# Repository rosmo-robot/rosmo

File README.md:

# Rosmo
 Rosmo Hardware
 For documentation see [https://rosmo-robot.github.io/](https://rosmo-robot.github.io/)

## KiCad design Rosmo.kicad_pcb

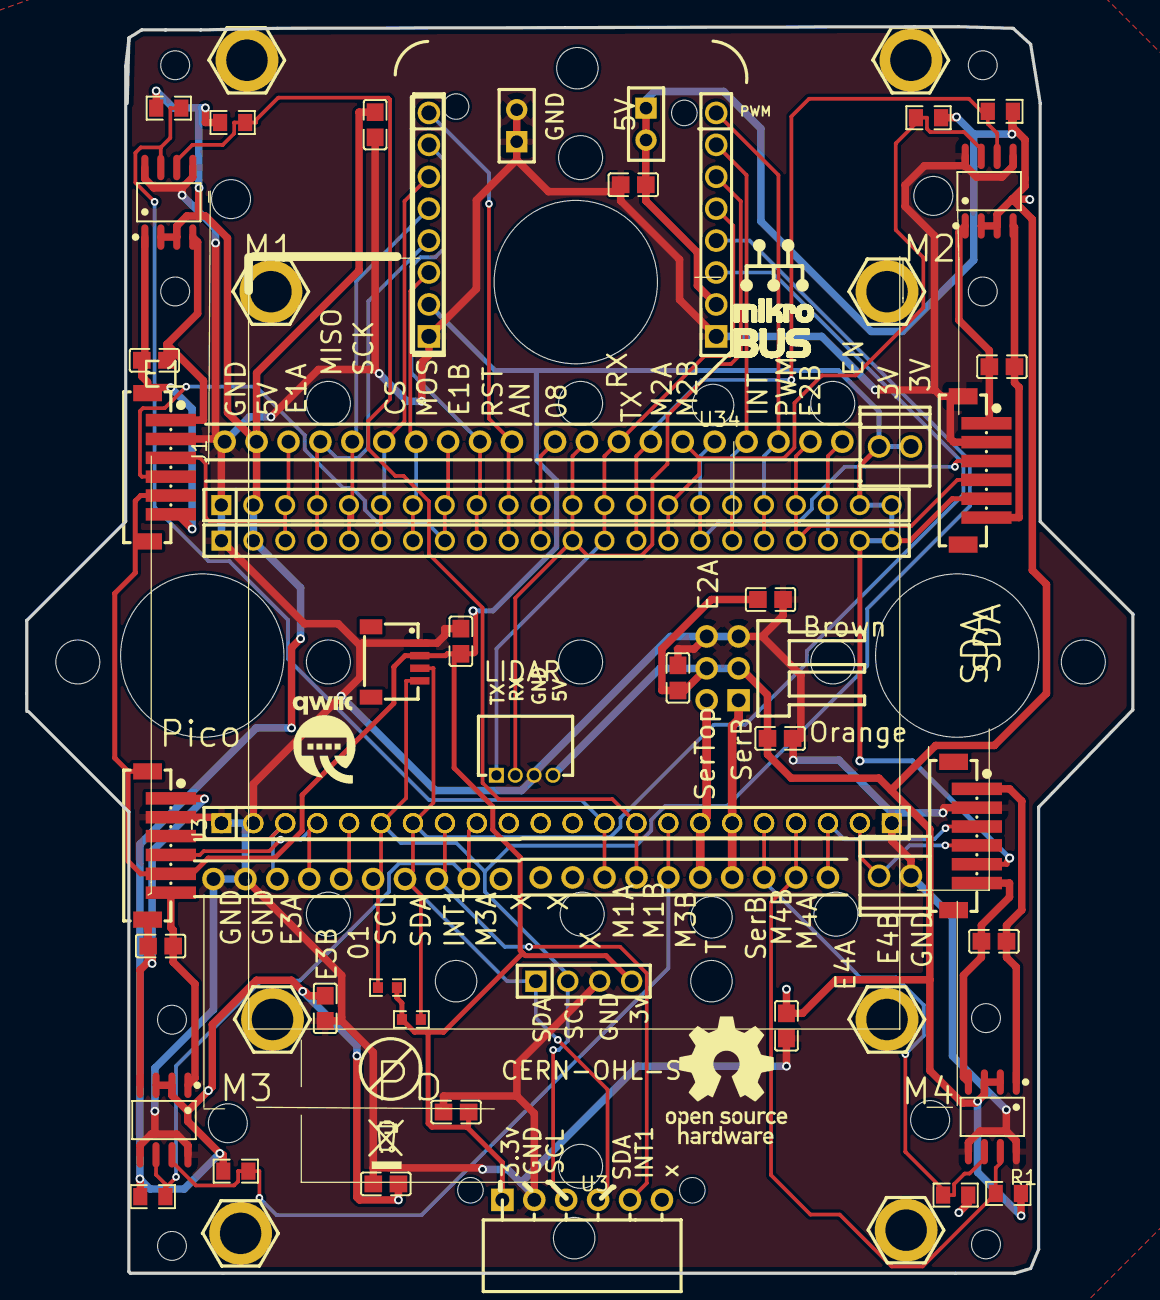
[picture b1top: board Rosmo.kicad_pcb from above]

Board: 2 copper layers, 88.0 x 99.2 mm, 78 parts (0 on the bottom side), 45 nets.

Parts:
.5: OPENSOURCE-LOGO-TOP
C1, C6: C440198; C0805
C2, C3, C4, C5, C7, C8, C9, C10, C12, C14, C15, C16: C49678; C0805
H3, H4: C27438; HDR-TH_8P-P2.54-V-F-1
H6: C2894983; HDR-TH_6P-P2.54-H-M-R2-C3-S2.54-W12.3-N
J1, J2, J3, J4: C2904998; CONN-SMD_6P-P1.50_DEALON_ZH-6PS
J5: CONN-SMD_4P-P1.00_SM04B-SRSS-TB-LF-SN
LOGO1: WEEE_4MM
LOGO5: OSHW-LOGO-L
P3: C2897365; HDR-TH_2P-P2.54-V-F
P4: C49661; HDR-TH_2P-P2.54-V-F
QWIIC-LOGO-MEDIUM1: QWIIC-LOGO-MEDIUM
R1, R2, R5, R6, R7, R8, R9, R11: C17414; R0805
R3, R12: C25804; R0603
U2: Pb; LEADFREE
U3: C2833720; HDR-TH_6P-P2.54-H-F-W5.7
U5: HDR-TH_22P-P2.54-V-F
U6, U45, U48, U49: C2895059; SOP-8_L5.0-W4.0-P1.27-LS6.0-BL
U7, U50, U51: C2886702; HDR-TH_22P-P2.54-V-F
U8, U9, U22, U23: RECTANGULAR_HOLE
U11, U12, U15, U17, U18, U19, U25, U26: M3_STANDOFF
U13, U14: CONN-TH_DG308-2.54-02P-14-00A
U16: C2718488; HDR-TH_4P-P2.54-V-F
U20, U21, U24, U39: N20-40MM-WHEEL
U28, U34, U52, U53: CONN-TH_DB125-2.54-10P-GN
U33: C2845567; CONN-TH_4P-P1.50_HCTL_HC-ZH1.5-4AW
U35: PWM; MIKROBUS_SILK
U38: ORP ROSMO - NO EXTRA
U44, U46, U47, U54: HOLECUT

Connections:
01: U5.18, U51.5, U52.6
3V: C8.1, C12.1, H3.2, J1.5, J1.8, J2.5, J3.5, J3.7, J4.5, J5.2, R3.1, R12.2, U3.1, U7.21, U7.22, U13.1, U13.2, U16.4, U50.21, U50.22
08: U7.11, U34.1, U50.11
AN: H3.8, U7.10, U28.10, U50.10
CLK: H3.5, U7.5, U28.5, U50.5
CS: H3.6, U7.6, U28.6, U50.6
E1A: J1.3, U7.3, U28.3, U50.3
E1B: J1.4, U7.8, U28.8, U50.8
E2A: J2.3, U7.16, U34.6, U50.16
E2B: J2.4, U7.19, U34.9, U50.19
E3A: J3.3, U5.20, U51.3, U52.8
E3B: J3.4, U5.19, U51.4, U52.7
E4A: J4.3, U5.3, U51.20, U53.1
E4B: J4.4, U5.2, U14.1, U51.21
EN: U7.20, U34.10, U50.20
GND: C1.1, C6.1, C7.1, C8.2, C9.2, C10.2, C12.2, C14.2, C15.2, C16.2, H3.1, H4.1, H6.5, H6.6, J1.2, J2.2, J2.7, J3.2, J4.2, J5.1, P3.1, P3.2, U3.2, U5.1, U5.21, U5.22, U6.5, U6.8, U7.1, U14.2, U16.3, U28.1, U33.3, U45.5, U45.8, U48.5, U48.8, U49.5, U49.8, U50.1, U51.1, U51.2, U51.22, U52.9, U52.10
INT: H4.7, U7.17, U34.7, U50.17
INT1: U3.5, U5.15, U51.8, U52.3
L1: C1.2, C6.2, C7.2, C9.1, C10.1, C14.1, C15.1, C16.1, H4.2, H6.3, H6.4, P4.1, P4.2, R1.2, R2.2, R5.1, R6.1, R7.1, R8.1, R9.1, R11.2, U6.2, U6.3, U7.2, U28.2, U33.4, U45.2, U45.3, U48.2, U48.3, U49.2, U49.3, U50.2
M1A: C3.1, J1.6, J1.7, U45.1
M1B: C3.2, J1.1, U45.4
M1CA: R5.2, U5.10, U45.7, U51.13, U53.8
M1CB: R6.2, U5.9, U45.6, U51.14, U53.7
M2A: C2.2, J2.6, U6.4
M2B: C2.1, J2.1, U6.1
M2CA: R2.1, U6.6, U7.14, U34.4, U50.14
M2CB: R11.1, U6.7, U7.15, U34.5, U50.15
M3A: C4.1, J3.1, J3.8, U48.4
M3B: C4.2, J3.6, U48.1
M3CA: R7.2, U5.14, U48.6, U51.9, U52.2
M3CB: R8.2, U5.8, U48.7, U51.15, U53.6
M4A: C5.2, J4.1, U49.1
M4B: C5.1, J4.6, U49.4
M4CB: R9.2, U5.5, U49.6, U51.18, U53.3
MC4A: R1.1, U5.4, U49.7, U51.19, U53.2
MISO: H3.4, U7.4, U28.4, U50.4
MOSI: H3.3, U7.7, U28.7, U50.7
PWM: H4.8, U7.18, U34.8, U50.18
RST: H3.7, U7.9, U28.9, U50.9
RX: H4.6, U7.12, U33.2, U34.2, U50.12
SCL: H4.4, J5.4, R12.1, U3.3, U5.17, U16.2, U51.6, U52.5
SDA: H4.3, J5.3, R3.2, U3.4, U5.16, U16.1, U51.7, U52.4
SERB: H6.1, U5.6, U51.17, U53.4
SERT: H6.2, U5.7, U51.16, U53.5
TX: H4.5, U7.13, U33.1, U34.3, U50.13

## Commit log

2024-04-09 Hardware
2024-04-11 Added build photos
2024-04-16 Added JLPCB production files
2024-05-02 Backup of Easyeda

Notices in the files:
Rosmo.kicad_pcb:
CERN-OHL-S
